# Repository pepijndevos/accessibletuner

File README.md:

# accessibletuner
Accessible Guitar Tuner

[Project page](https://hackaday.io/project/26255-accesible-guitar-tuner)

## Bountysource

Please get in touch if you want to help. I may be able to send you a PCB, put up additional bounties or make other arrangements.

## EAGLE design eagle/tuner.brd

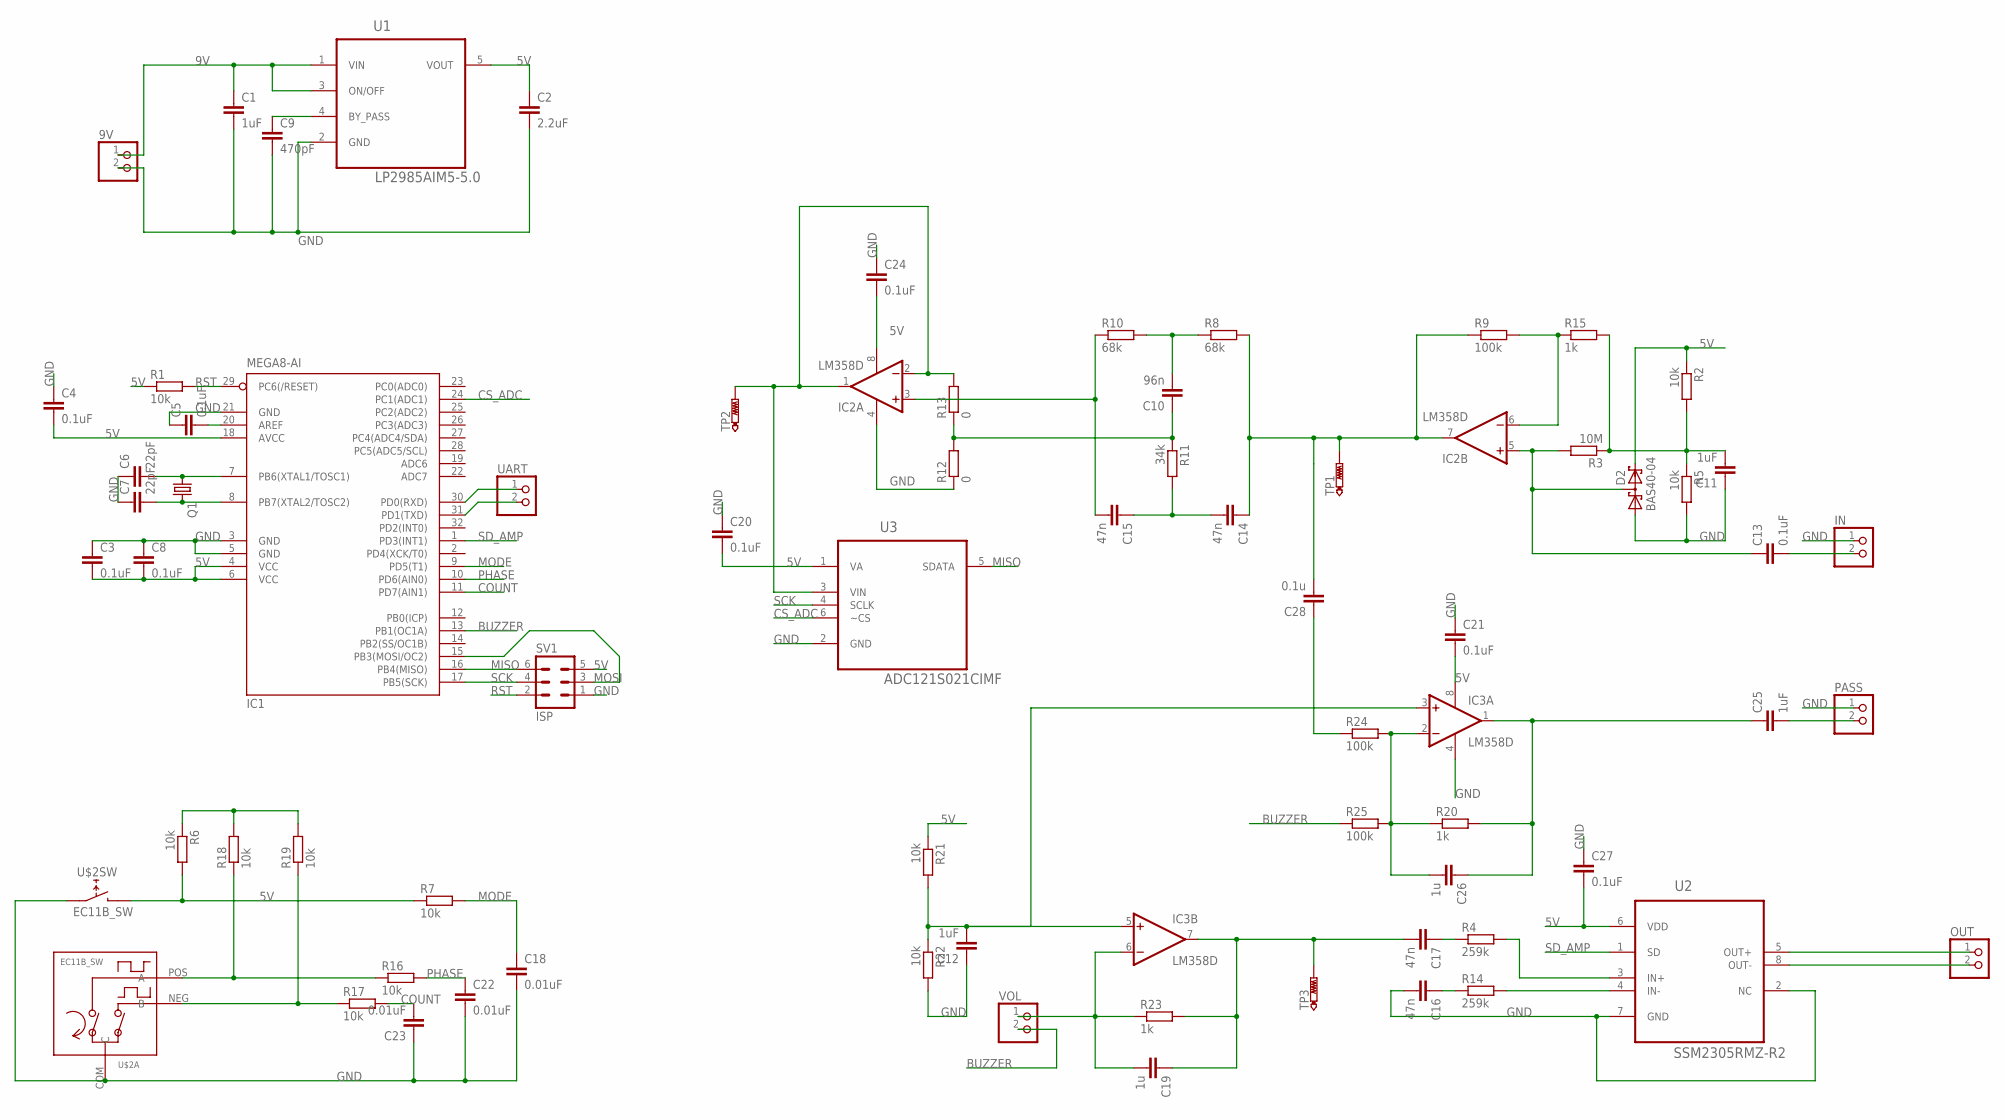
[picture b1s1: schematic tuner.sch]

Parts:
9V: PINHD-1X2; 1X02
C1, C11, C12, C25: 1uF; C0805
C2: 2.2uF; C0805
C3, C4, C5, C8, C13, C20, C21, C24, C27: 0.1uF; C0805
C6, C7: 22pF; C0805
C9: 470pF; C0805
C10: 96n; C0805
C14, C15, C16, C17: 47n; C0805
C18, C22, C23: 0.01uF; C0805
C19, C26: 1u; C0805
C28: 0.1u; C0805
D2: BAS40-04; SOT23
IC1: MEGA8-AI; TQFP32-08
IC2, IC3: LM358D; SO08
IN: PINHD-1X2; 1X02
OUT: PINHD-1X2; 1X02
PASS: PINHD-1X2; 1X02
Q1: CRYSTALHC49S; HC49/S
R1, R2, R5, R6, R7, R16, R17, R18, R19, R21, R22: 10k; M0805
R3: 10M; M0805
R4, R14: 259k; M0805
R8, R10: 68k; M0805
R9, R24, R25: 100k; M0805
R11: 34k; M0805
R12, R13: 0; M0805
R15, R20, R23: 1k; M0805
SV1: ISP; MA03-2
TP1, TP2, TP3: PTR1B1,27; B1,27
U1: LP2985AIM5-5.0; SOT95P284X119-5N
U2: SSM2305RMZ-R2; SOP65P490X110-8N
U3: ADC121S021CIMF; SOT95P284X122-6N
U$2: EC11B_SW; EC11B
UART: PINHD-1X2; 1X02
VOL: PINHD-1X2; 1X02

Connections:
5V: C2.1, C3.2, C4.2, C8.2, C20.2, C21.2, C24.2, C27.2, D2.2 (C2), IC1.4 (VCC), IC1.6 (VCC), IC1.18 (AVCC), IC2.8 (V+), IC3.8 (V+), R1.1, R2.1, R6.1, R18.2, R19.2, R21.1, SV1.5, U1.5 (VOUT), U2.6 (VDD), U3.1 (VA)
9V: 9V.1, C1.1, U1.1 (VIN), U1.3 (ON/OFF)
BUZZER: IC1.13 (PB1(OC1A)), R25.1, VOL.2
COUNT: C23.2, IC1.11 (PD7(AIN1)), R17.2
CS_ADC: IC1.24 (PC1(ADC1)), U3.6 (~CS)
FG: C10.1, R11.1, R12.2, R13.1
GND: 9V.2, C1.2, C2.2, C3.1, C4.1, C5.1, C6.1, C7.1, C8.1, C9.2, C11.1, C12.1, C16.2, C18.2, C20.1, C21.1, C22.2, C23.1, C24.1, C27.1, D2.1 (A1), IC1.3 (GND), IC1.5 (GND), IC1.21 (GND), IC2.4 (V-), IC3.4 (V-), IN.1, PASS.1, R5.2, R12.1, R22.2, SV1.1, U1.2 (GND), U2.2 (NC), U2.7 (GND), U3.2 (GND), U$2.COM (C), U$2.SW1 (D)
MISO: IC1.16 (PB4(MISO)), SV1.6, U3.5 (SDATA)
MODE: C18.1, IC1.9 (PD5(T1)), R7.2
MOSI: IC1.15 (PB3(MOSI/OC2)), SV1.3
unnamed: C28.1, R24.1
unnamed: C9.1, U1.4 (BY_PASS)
unnamed: C5.2, IC1.20 (AREF)
unnamed: C6.2, IC1.7 (PB6(XTAL1/TOSC1)), Q1.1
unnamed: C7.2, IC1.8 (PB7(XTAL2/TOSC2)), Q1.2
unnamed: C17.2, C19.1, IC3.7 (OUT), R23.2, TP3.TP
unnamed: C19.2, IC3.6 (-IN), R23.1, VOL.1
unnamed: C12.2, IC3.3 (+IN), IC3.5 (+IN), R21.2, R22.1
unnamed: OUT.1, U2.5 (OUT+)
unnamed: C14.1, C28.2, IC2.7 (OUT), R8.2, R9.1, TP1.TP
unnamed: OUT.2, U2.8 (OUT-)
unnamed: C13.2, IN.2
unnamed: IC2.6 (-IN), R9.2, R15.1
unnamed: R4.2, U2.3 (IN+)
unnamed: C25.2, PASS.2
unnamed: C13.1, D2.3 (C1A2), IC2.5 (+IN), R3.2
unnamed: C11.2, R2.2, R3.1, R5.1, R15.2
unnamed: C25.1, C26.1, IC3.1 (OUT), R20.2
unnamed: C14.2, C15.1, R11.2
unnamed: C15.2, IC2.3 (+IN), R10.1
unnamed: R14.2, U2.4 (IN-)
unnamed: R16.1, R18.1, U$2.POS (A)
unnamed: R17.1, R19.1, U$2.NEG (B)
unnamed: IC1.30 (PD0(RXD)), UART.1
unnamed: C10.2, R8.1, R10.2
unnamed: IC1.31 (PD1(TXD)), UART.2
unnamed: C16.1, R14.1
unnamed: IC2.1 (OUT), IC2.2 (-IN), R13.2, TP2.TP, U3.3 (VIN)
unnamed: C17.1, R4.1
unnamed: C26.2, IC3.2 (-IN), R20.1, R24.2, R25.2
unnamed: R6.2, R7.1, U$2.SW2 (E)
PHASE: C22.1, IC1.10 (PD6(AIN0)), R16.2
RST: IC1.29 (PC6(/RESET)), R1.2, SV1.2
SCK: IC1.17 (PB5(SCK)), SV1.4, U3.4 (SCLK)
SD_AMP: IC1.1 (PD3(INT1)), U2.1 (SD)

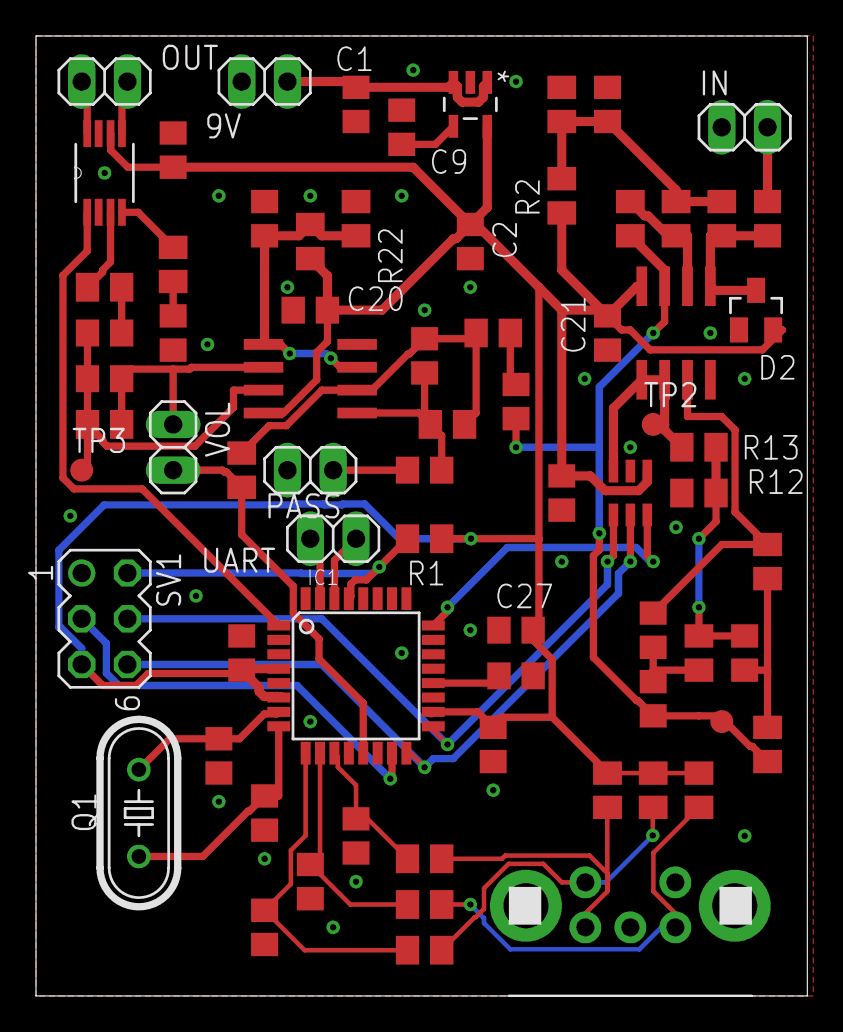
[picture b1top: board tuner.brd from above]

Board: 2 copper layers, 42.8 x 53.3 mm, 72 parts (0 on the bottom side), 45 nets.

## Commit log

2017-07-07 broken stuff
2017-07-07 sine works
2017-07-07 ITS WORKING... A BIT
2017-07-10 initial lowpass filter with brokencoefficients
2017-07-10 Working things using envelope detection
2017-07-12 tone selection and simulation
2017-07-12 modify for 328
2017-07-12 update simulation for second prototype
2017-07-13 improve volume and fix note selection on 328
2017-07-14 updated PCB
2017-07-25 move pins around for PCB
2017-07-26 spi slave
2017-07-26 set SPI pins
2017-07-26 dynamic threshold adjustment
2017-07-27 improved power supply noise rejection
2017-08-02 update schematic with agc and high-z input, D-class out
2017-08-02 second revision
2017-08-02 ordered
2017-09-16 update for new pcb
2017-09-19 add misc simulation files
2017-09-20 add LTSpice files
2017-11-12 upate simulation
2017-11-18 input mic sim [pop]
2018-01-03 work on next revision PCB
2018-01-04 do board layout
2018-01-05 lemme smash
2018-02-03 update for hardware rev3
2018-02-08 this should be 11 I'm pretty sure
2018-02-17 attempt IIR
2018-02-17 IIR testing
2018-02-18 get rid of timer interrupt
2018-02-18 fix those indices, idiot
2018-02-18 sortof maybe working code, bad LPF
2018-02-18 improve filter slightly. Output broke somewhere along the way
2018-02-18 sortof working code without minimum amplitude or normalization
2018-02-18 commit actual working iir filter
2018-02-18 P E R F E C T (ish)
2018-02-25 fix overflow and multiplication
2018-07-16 fix negative tones
2018-07-16 semitone mode
